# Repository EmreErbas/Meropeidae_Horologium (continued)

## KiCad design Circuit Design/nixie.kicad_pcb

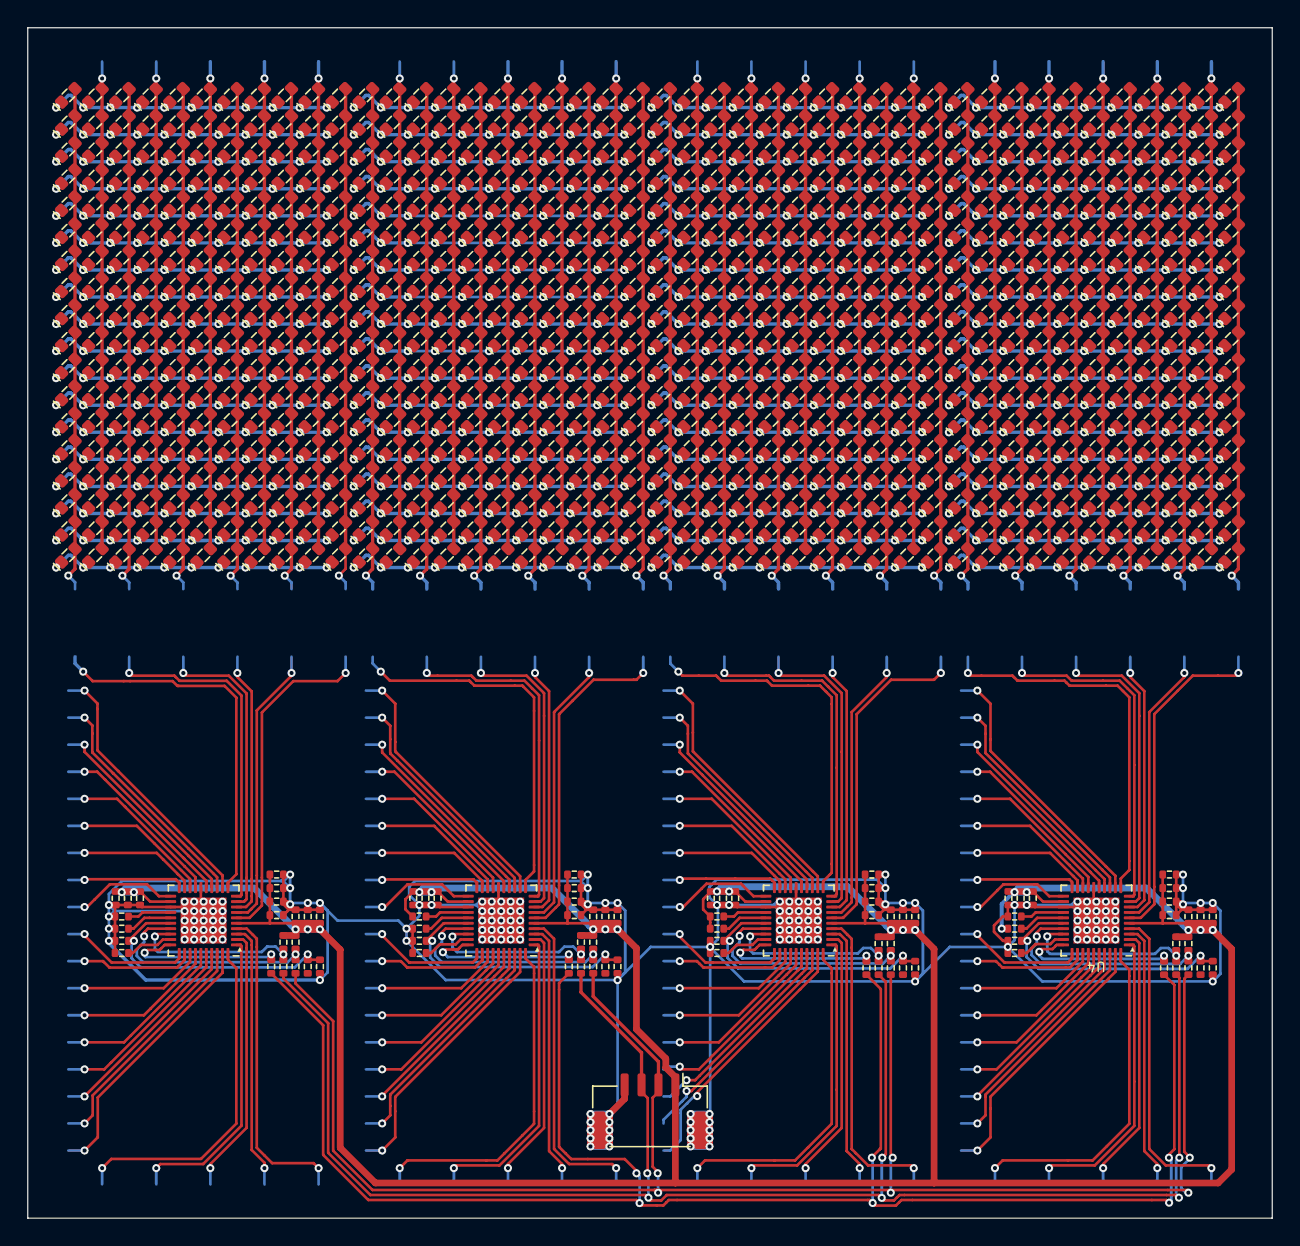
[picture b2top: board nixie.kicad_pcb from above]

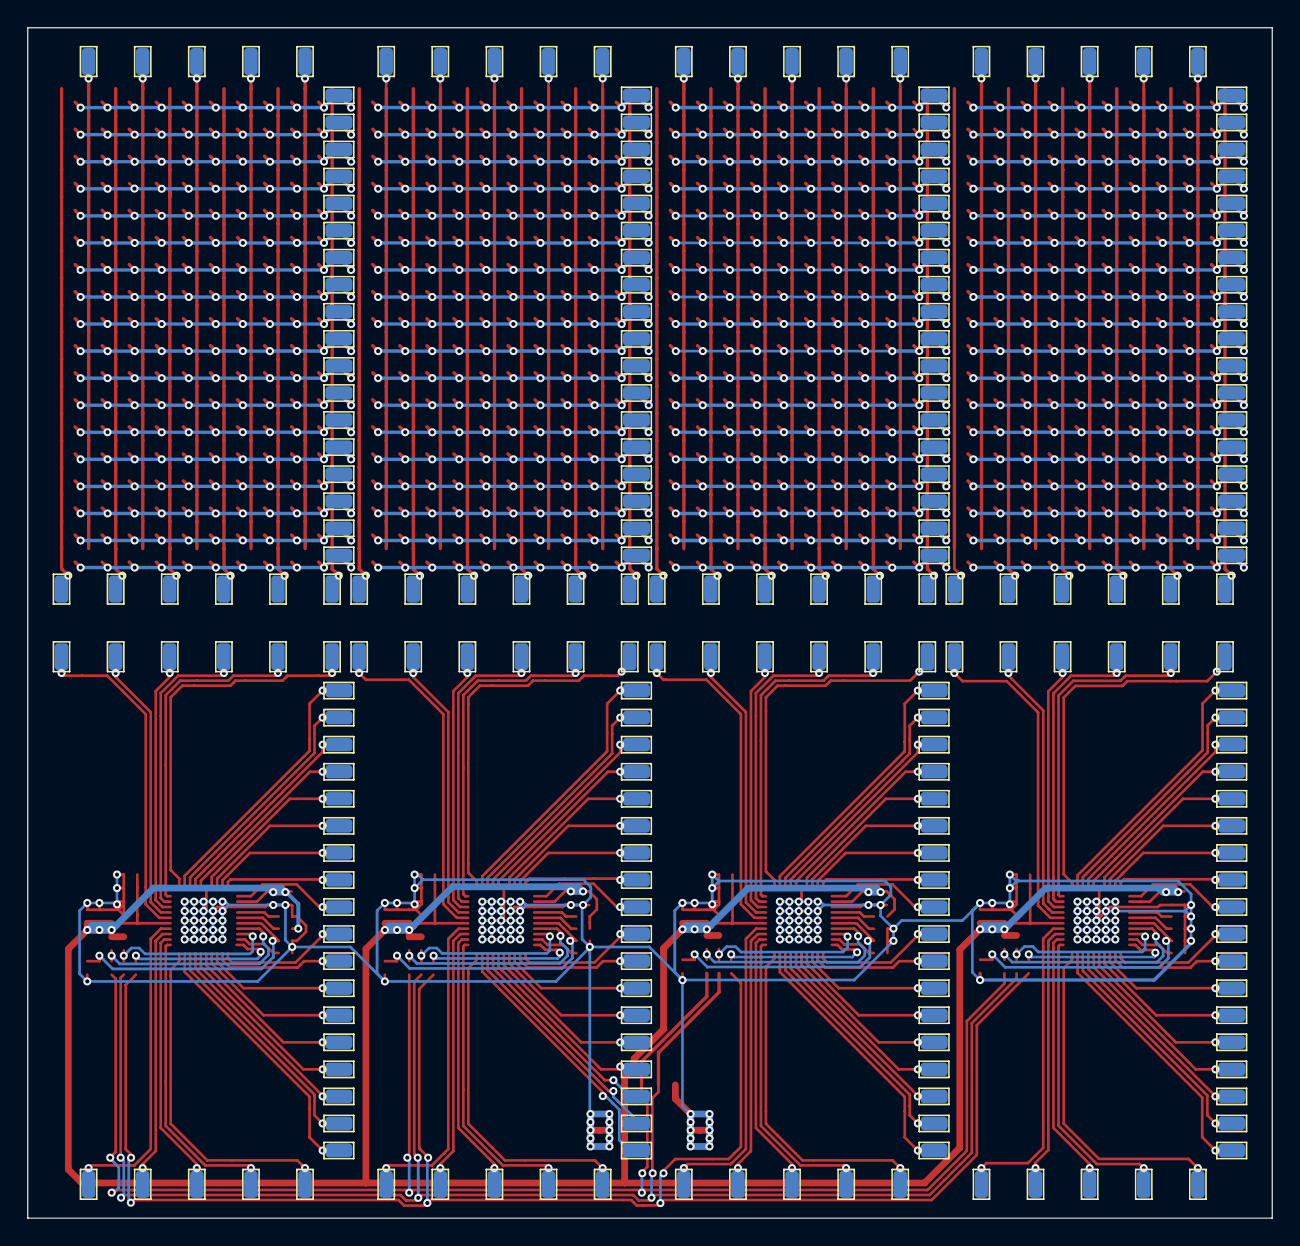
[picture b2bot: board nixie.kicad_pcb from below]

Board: 2 copper layers, 92.0 x 88.0 mm, 1113 parts (232 on the bottom side), 265 nets.

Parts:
C1, C2, C3, C4, C5, C6, C7, C8, C9, C10, C11, C12, C13, C16, C20, C23, C27, C30, C34, C35, C36, C37, C38, C41: 1uF; C-0402
C14, C15, C17, C18, C19, C21, C22, C24, C25, C26, C28, C29, C31, C32, C33, C39, C40, C42, C43, C44: 100nF; C-0402
CP1, CP2, CP3, CP4, CP5, CP6, CP7, CP8, CP9, CP10, CP11, CP12, CP13, CP14, CP15, CP16, CP17, CP18, CP19, CP20, CP21, CP22, CP23, CP24, CP25, CP26, CP27, CP28, CP29, CP30, CP31, CP32, CP33, CP34, CP35, CP36, CP37, CP38, CP39, CP40, CP41, CP42, CP43, CP44, CP45, CP46, CP47, CP48, CP49, CP50, CP51, CP52, CP53, CP54, CP55, CP56, CP57, CP58, CP59, CP60, CP61, CP62, CP63, CP64, CP65, CP66, CP67, CP68, CP69, CP70, CP71, CP72, CP73, CP74, CP75, CP76, CP77, CP78, CP79, CP80, CP81, CP82, CP83, CP84, CP85, CP86, CP87, CP88, CP89, CP90, CP91, CP92, CP93, CP94, CP95, CP96, CP97, CP98, CP99, CP100, CP101, CP102, CP103, CP104, CP105, CP106, CP107, CP108, CP109, CP110, CP111, CP112, CP113, CP114, CP115, CP116, CP117, CP118, CP119, CP120, CP121, CP122, CP123, CP124, CP125, CP126, CP127, CP128, CP129, CP130, CP131, CP132, CP133, CP134, CP135, CP136, CP137, CP138, CP139, CP140, CP141, CP142, CP143, CP144, CP145, CP146, CP147, CP148, CP149, CP150, CP151, CP152, CP153, CP154, CP155, CP156, CP157, CP158, CP159, CP160, CP161, CP162, CP163, CP164, CP165, CP166, CP167, CP168, CP169, CP170, CP171, CP172, CP173, CP174, CP175, CP176, CP177, CP178, CP179, CP180, CP181, CP182, CP183, CP184, CP185, CP186, CP187, CP188, CP189, CP190, CP191, CP192, CP193, CP194, CP195, CP196, CP197, CP198, CP199, CP200, CP201, CP202, CP203, CP204, CP205, CP206, CP207, CP208, CP209, CP210, CP211, CP212, CP213, CP214, CP215, CP216, CP217, CP218, CP219, CP220, CP221, CP222, CP223, CP224, CP225, CP226, CP227, CP228, CP229, CP230, CP231, CP232: SolderPad; SolderPt_1x2mm
D1, D2, D3, D4, D5, D6, D7, D8, D9, D10, D11, D12, D13, D14, D15, D16, D17, D18, D19, D20, D21, D22, D23, D24, D25, D26, D27, D28, D29, D30, D31, D32, D33, D34, D35, D36, D37, D38, D39, D40, D41, D42, D43, D44, D45, D46, D47, D48, D49, D50, D51, D52, D53, D54, D55, D56, D57, D58, D59, D60, D61, D62, D63, D64, D65, D66, D67, D68, D69, D70, D71, D72, D73, D74, D75, D76, D77, D78, D79, D80, D81, D82, D83, D84, D85, D86, D87, D88, D89, D90, D91, D92, D93, D94, D95, D96, D97, D98, D99, D100, D101, D102, D103, D104, D105, D106, D107, D108, D109, D110, D111, D112, D113, D114, D115, D116, D117, D118, D119, D120, D121, D122, D123, D124, D125, D126, D127, D128, D129, D130, D131, D132, D133, D134, D135, D136, D137, D138, D139, D140, D141, D142, D143, D144, D145, D146, D147, D148, D149, D150, D151, D152, D153, D154, D155, D156, D157, D158, D159, D160, D161, D162, D163, D164, D165, D166, D167, D168, D169, D170, D171, D172, D173, D174, D175, D176, D177, D178, D179, D180, D181, D182, D183, D184, D185, D186, D187, D188, D189, D190, D191, D192, D193, D194, D195, D196, D197, D198, D199, D200, D201, D202, D203, D204, D205, D206, D207, D208, D209, D210, D211, D212, D213, D214, D215, D216, D217, D218, D219, D220, D221, D222, D223, D224, D225, D226, D227, D228, D229, D230, D231, D232, D233, D234, D235, D236, D237, D238, D239, D240, D241, D242, D243, D244, D245, D246, D247, D248, D249, D250, D251, D252, D253, D254, D255, D256, D257, D258, D259, D260, D261, D262, D263, D264, D265, D266, D267, D268, D269, D270, D271, D272, D273, D274, D275, D276, D277, D278, D279, D280, D281, D282, D283, D284, D285, D286, D287, D288, D289, D290, D291, D292, D293, D294, D295, D296, D297, D298, D299, D300, D301, D302, D303, D304, D305, D306, D307, D308, D309, D310, D311, D312, D313, D314, D315, D316, D317, D318, D319, D320, D321, D322, D323, D324, D325, D326, D327, D328, D329, D330, D331, D332, D333, D334, D335, D336, D337, D338, D339, D340, D341, D342, D343, D344, D345, D346, D347, D348, D349, D350, D351, D352, D353, D354, D355, D356, D357, D358, D359, D360, D361, D362, D363, D364, D365, D366, D367, D368, D369, D370, D371, D372, D373, D374, D375, D376, D377, D378, D379, D380, D381, D382, D383, D384, D385, D386, D387, D388, D389, D390, D391, D392, D393, D394, D395, D396, D397, D398, D399, D400, D401, D402, D403, D404, D405, D406, D407, D408, D409, D410, D411, D412, D413, D414, D415, D416, D417, D418, D419, D420, D421, D422, D423, D424, D425, D426, D427, D428, D429, D430, D431, D432, D433, D434, D435, D436, D437, D438, D439, D440, D441, D442, D443, D444, D445, D446, D447, D448, D449, D450, D451, D452, D453, D454, D455, D456, D457, D458, D459, D460, D461, D462, D463, D464, D465, D466, D467, D468, D469, D470, D471, D472, D473, D474, D475, D476, D477, D478, D479, D480, D481, D482, D483, D484, D485, D486, D487, D488, D489, D490, D491, D492, D493, D494, D495, D496, D497, D498, D499, D500, D501, D502, D503, D504, D505, D506, D507, D508, D509, D510, D511, D512, D513, D514, D515, D516, D517, D518, D519, D520, D521, D522, D523, D524, D525, D526, D527, D528, D529, D530, D531, D532, D533, D534, D535, D536, D537, D538, D539, D540, D541, D542, D543, D544, D545, D546, D547, D548, D549, D550, D551, D552, D553, D554, D555, D556, D557, D558, D559, D560, D561, D562, D563, D564, D565, D566, D567, D568, D569, D570, D571, D572, D573, D574, D575, D576, D577, D578, D579, D580, D581, D582, D583, D584, D585, D586, D587, D588, D589, D590, D591, D592, D593, D594, D595, D596, D597, D598, D599, D600, D601, D602, D603, D604, D605, D606, D607, D608, D609, D610, D611, D612, D613, D614, D615, D616, D617, D618, D619, D620, D621, D622, D623, D624, D625, D626, D627, D628, D629, D630, D631, D632, D633, D634, D635, D636, D637, D638, D639, D640, D641, D642, D643, D644, D645, D646, D647, D648, D649, D650, D651, D652, D653, D654, D655, D656, D657, D658, D659, D660, D661, D662, D663, D664, D665, D666, D667, D668, D669, D670, D671, D672, D673, D674, D675, D676, D677, D678, D679, D680, D681, D682, D683, D684, D685, D686, D687, D688, D689, D690, D691, D692, D693, D694, D695, D696, D697, D698, D699, D700, D701, D702, D703, D704, D705, D706, D707, D708, D709, D710, D711, D712, D713, D714, D715, D716, D717, D718, D719, D720, D721, D722, D723, D724, D725, D726, D727, D728, D729, D730, D731, D732, D733, D734, D735, D736, D737, D738, D739, D740, D741, D742, D743, D744, D745, D746, D747, D748, D749, D750, D751, D752, D753, D754, D755, D756, D757, D758, D759, D760, D761, D762, D763, D764, D765, D766, D767, D768, D769, D770, D771, D772, D773, D774, D775, D776, D777, D778, D779, D780, D781, D782, D783, D784, D785, D786, D787, D788, D789, D790, D791, D792: LED_A; LED-0603
J1: BM04B-GHS-TBT
R1, R2, R11, R12, R21, R22, R31, R32: 10K; R-0402
R3, R4, R5, R13, R14, R15, R23, R24, R25, R33, R34, R35: 22R; R-0402
R6, R16, R26, R36: 100K; R-0402
R7, R9, R10, R17, R19, R20, R27, R29, R30, R37, R39, R40: 0R; R-0402
R8, R18, R28, R38: 18K; R-0402
U1, U2, U3, U4: IS31FL3743A; QFN-40-EP

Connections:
+3V3: C1.1, C2.1, C3.1, C4.1, C5.1, C6.1, C7.1, C8.1, C9.1, C10.1, C11.1, C12.1, C13.1, C14.1, C15.1, C16.1, C17.1, C18.1, C20.1, C21.1, C22.1, C23.1, C24.1, C25.1, C27.1, C28.1, C29.1, C30.1, C31.1, C32.1, C34.1, C35.1, C36.1, C37.1, C38.1, C39.1, C40.1, C41.1, C42.1, C43.1, J1.1, R1.1, R2.1, R11.1, R12.1, R19.1, R21.1, R22.1, R29.1, R30.1, R31.1, R32.1, R40.1, U1.5 (PVCC), U1.22 (VCC), U2.5 (PVCC), U2.22 (VCC), U3.5 (PVCC), U3.22 (VCC), U4.5 (PVCC), U4.22 (VCC)
/LED Driver1/CS1: CP171.1, U2.39 (CS1)
/LED Driver1/CS2: CP165.1, U2.38 (CS2)
/LED Driver1/CS3: CP159.1, U2.37 (CS3)
/LED Driver1/CS4: CP153.1, U2.36 (CS4)
/LED Driver1/CS5: CP147.1, U2.35 (CS5)
/LED Driver1/CS6: CP141.1, U2.34 (CS6)
/LED Driver1/CS7: CP135.1, U2.33 (CS7)
/LED Driver1/CS8: CP129.1, U2.32 (CS8)
/LED Driver1/CS9: CP123.1, U2.31 (CS9)
/LED Driver1/CS10: CP117.1, U2.21 (CS10)
/LED Driver1/CS11: CP111.1, U2.20 (CS11)
/LED Driver1/CS12: CP105.1, U2.19 (CS12)
/LED Driver1/CS13: CP99.1, U2.18 (CS13)
/LED Driver1/CS14: CP93.1, U2.17 (CS14)
/LED Driver1/CS15: CP87.1, U2.15 (CS15)
/LED Driver1/CS16: CP81.1, U2.14 (CS16)
/LED Driver1/CS17: CP75.1, U2.13 (CS17)
/LED Driver1/CS18: CP69.1, U2.12 (CS18)
/LED Driver1/SW1: CP3.1, U2.6 (SW1)
/LED Driver1/SW2: CP9.1, U2.4 (SW2)
/LED Driver1/SW3: CP15.1, U2.7 (SW3)
/LED Driver1/SW4: CP21.1, U2.3 (SW4)
/LED Driver1/SW5: CP27.1, U2.8 (SW5)
/LED Driver1/SW6: CP33.1, U2.2 (SW6)
/LED Driver1/SW7: CP39.1, U2.9 (SW7)
/LED Driver1/SW8: CP45.1, U2.1 (SW8)
/LED Driver1/SW9: CP51.1, U2.10 (SW9)
/LED Driver1/SW10: CP57.1, U2.40 (SW10)
/LED Driver1/SW11: CP63.1, U2.11 (SW11)
/LED Driver2/CS1: CP173.1, U3.39 (CS1)
/LED Driver2/CS2: CP167.1, U3.38 (CS2)
/LED Driver2/CS3: CP161.1, U3.37 (CS3)
/LED Driver2/CS4: CP155.1, U3.36 (CS4)
/LED Driver2/CS5: CP149.1, U3.35 (CS5)
/LED Driver2/CS6: CP143.1, U3.34 (CS6)
/LED Driver2/CS7: CP137.1, U3.33 (CS7)
/LED Driver2/CS8: CP131.1, U3.32 (CS8)
/LED Driver2/CS9: CP125.1, U3.31 (CS9)
/LED Driver2/CS10: CP119.1, U3.21 (CS10)
/LED Driver2/CS11: CP113.1, U3.20 (CS11)
/LED Driver2/CS12: CP107.1, U3.19 (CS12)
/LED Driver2/CS13: CP101.1, U3.18 (CS13)
/LED Driver2/CS14: CP95.1, U3.17 (CS14)
/LED Driver2/CS15: CP89.1, U3.15 (CS15)
/LED Driver2/CS16: CP83.1, U3.14 (CS16)
/LED Driver2/CS17: CP77.1, U3.13 (CS17)
/LED Driver2/CS18: CP71.1, U3.12 (CS18)
/LED Driver2/SW1: CP5.1, U3.6 (SW1)
/LED Driver2/SW2: CP11.1, U3.4 (SW2)
/LED Driver2/SW3: CP17.1, U3.7 (SW3)
/LED Driver2/SW4: CP23.1, U3.3 (SW4)
/LED Driver2/SW5: CP29.1, U3.8 (SW5)
/LED Driver2/SW6: CP35.1, U3.2 (SW6)
/LED Driver2/SW7: CP41.1, U3.9 (SW7)
/LED Driver2/SW8: CP47.1, U3.1 (SW8)
/LED Driver2/SW9: CP53.1, U3.10 (SW9)
/LED Driver2/SW10: CP59.1, U3.40 (SW10)
/LED Driver2/SW11: CP65.1, U3.11 (SW11)
/LED Driver3/CS1: CP231.1, U4.39 (CS1)
/LED Driver3/CS2: CP229.1, U4.38 (CS2)
/LED Driver3/CS3: CP227.1, U4.37 (CS3)
/LED Driver3/CS4: CP225.1, U4.36 (CS4)
/LED Driver3/CS5: CP223.1, U4.35 (CS5)
/LED Driver3/CS6: CP221.1, U4.34 (CS6)
/LED Driver3/CS7: CP219.1, U4.33 (CS7)
/LED Driver3/CS8: CP217.1, U4.32 (CS8)
/LED Driver3/CS9: CP215.1, U4.31 (CS9)
/LED Driver3/CS10: CP213.1, U4.21 (CS10)
/LED Driver3/CS11: CP211.1, U4.20 (CS11)
/LED Driver3/CS12: CP209.1, U4.19 (CS12)
/LED Driver3/CS13: CP207.1, U4.18 (CS13)
/LED Driver3/CS14: CP205.1, U4.17 (CS14)
/LED Driver3/CS15: CP203.1, U4.15 (CS15)
/LED Driver3/CS16: CP201.1, U4.14 (CS16)
/LED Driver3/CS17: CP199.1, U4.13 (CS17)
/LED Driver3/CS18: CP197.1, U4.12 (CS18)
/LED Driver3/SW1: CP175.1, U4.6 (SW1)
/LED Driver3/SW2: CP177.1, U4.4 (SW2)
/LED Driver3/SW3: CP179.1, U4.7 (SW3)
/LED Driver3/SW4: CP181.1, U4.3 (SW4)
/LED Driver3/SW5: CP183.1, U4.8 (SW5)
/LED Driver3/SW6: CP185.1, U4.2 (SW6)
/LED Driver3/SW7: CP187.1, U4.9 (SW7)
/LED Driver3/SW8: CP189.1, U4.1 (SW8)
/LED Driver3/SW9: CP191.1, U4.10 (SW9)
/LED Driver3/SW10: CP193.1, U4.40 (SW10)
/LED Driver3/SW11: CP195.1, U4.11 (SW11)
/LED Driver/CS1: CP169.1, U1.39 (CS1)
/LED Driver/CS2: CP163.1, U1.38 (CS2)
/LED Driver/CS3: CP157.1, U1.37 (CS3)
/LED Driver/CS4: CP151.1, U1.36 (CS4)
/LED Driver/CS5: CP145.1, U1.35 (CS5)
/LED Driver/CS6: CP139.1, U1.34 (CS6)
/LED Driver/CS7: CP133.1, U1.33 (CS7)
/LED Driver/CS8: CP127.1, U1.32 (CS8)
/LED Driver/CS9: CP121.1, U1.31 (CS9)
/LED Driver/CS10: CP115.1, U1.21 (CS10)
/LED Driver/CS11: CP109.1, U1.20 (CS11)
/LED Driver/CS12: CP103.1, U1.19 (CS12)
/LED Driver/CS13: CP97.1, U1.18 (CS13)
/LED Driver/CS14: CP91.1, U1.17 (CS14)
/LED Driver/CS15: CP85.1, U1.15 (CS15)
/LED Driver/CS16: CP79.1, U1.14 (CS16)
/LED Driver/CS17: CP73.1, U1.13 (CS17)
/LED Driver/CS18: CP67.1, U1.12 (CS18)
/LED Driver/SW1: CP1.1, U1.6 (SW1)
/LED Driver/SW2: CP7.1, U1.4 (SW2)
/LED Driver/SW3: CP13.1, U1.7 (SW3)
/LED Driver/SW4: CP19.1, U1.3 (SW4)
/LED Driver/SW5: CP25.1, U1.8 (SW5)
/LED Driver/SW6: CP31.1, U1.2 (SW6)
/LED Driver/SW7: CP37.1, U1.9 (SW7)
/LED Driver/SW8: CP43.1, U1.1 (SW8)
/LED Driver/SW9: CP49.1, U1.10 (SW9)
/LED Driver/SW10: CP55.1, U1.40 (SW10)
/LED Driver/SW11: CP61.1, U1.11 (SW11)
/SCL: J1.2, R4.1, R14.1, R24.1, R34.1
/SDA: J1.3, R3.1, R13.1, R23.1, R33.1
/SYNC: R7.1, R17.1, R27.1, R37.1
/Screen1/CS1: CP172.1, D199.1 (K), D217.1 (K), D235.1 (K), D253.1 (K), D271.1 (K), D289.1 (K), D307.1 (K), D325.1 (K), D343.1 (K), D361.1 (K), D379.1 (K)
/Screen1/CS2: CP166.1, D200.1 (K), D218.1 (K), D236.1 (K), D254.1 (K), D272.1 (K), D290.1 (K), D308.1 (K), D326.1 (K), D344.1 (K), D362.1 (K), D380.1 (K)
/Screen1/CS3: CP160.1, D201.1 (K), D219.1 (K), D237.1 (K), D255.1 (K), D273.1 (K), D291.1 (K), D309.1 (K), D327.1 (K), D345.1 (K), D363.1 (K), D381.1 (K)
/Screen1/CS4: CP154.1, D202.1 (K), D220.1 (K), D238.1 (K), D256.1 (K), D274.1 (K), D292.1 (K), D310.1 (K), D328.1 (K), D346.1 (K), D364.1 (K), D382.1 (K)
/Screen1/CS5: CP148.1, D203.1 (K), D221.1 (K), D239.1 (K), D257.1 (K), D275.1 (K), D293.1 (K), D311.1 (K), D329.1 (K), D347.1 (K), D365.1 (K), D383.1 (K)
/Screen1/CS6: CP142.1, D204.1 (K), D222.1 (K), D240.1 (K), D258.1 (K), D276.1 (K), D294.1 (K), D312.1 (K), D330.1 (K), D348.1 (K), D366.1 (K), D384.1 (K)
/Screen1/CS7: CP136.1, D205.1 (K), D223.1 (K), D241.1 (K), D259.1 (K), D277.1 (K), D295.1 (K), D313.1 (K), D331.1 (K), D349.1 (K), D367.1 (K), D385.1 (K)
/Screen1/CS8: CP130.1, D206.1 (K), D224.1 (K), D242.1 (K), D260.1 (K), D278.1 (K), D296.1 (K), D314.1 (K), D332.1 (K), D350.1 (K), D368.1 (K), D386.1 (K)
/Screen1/CS9: CP124.1, D207.1 (K), D225.1 (K), D243.1 (K), D261.1 (K), D279.1 (K), D297.1 (K), D315.1 (K), D333.1 (K), D351.1 (K), D369.1 (K), D387.1 (K)
/Screen1/CS10: CP118.1, D208.1 (K), D226.1 (K), D244.1 (K), D262.1 (K), D280.1 (K), D298.1 (K), D316.1 (K), D334.1 (K), D352.1 (K), D370.1 (K), D388.1 (K)
/Screen1/CS11: CP112.1, D209.1 (K), D227.1 (K), D245.1 (K), D263.1 (K), D281.1 (K), D299.1 (K), D317.1 (K), D335.1 (K), D353.1 (K), D371.1 (K), D389.1 (K)
/Screen1/CS12: CP106.1, D210.1 (K), D228.1 (K), D246.1 (K), D264.1 (K), D282.1 (K), D300.1 (K), D318.1 (K), D336.1 (K), D354.1 (K), D372.1 (K), D390.1 (K)
/Screen1/CS13: CP100.1, D211.1 (K), D229.1 (K), D247.1 (K), D265.1 (K), D283.1 (K), D301.1 (K), D319.1 (K), D337.1 (K), D355.1 (K), D373.1 (K), D391.1 (K)
/Screen1/CS14: CP94.1, D212.1 (K), D230.1 (K), D248.1 (K), D266.1 (K), D284.1 (K), D302.1 (K), D320.1 (K), D338.1 (K), D356.1 (K), D374.1 (K), D392.1 (K)
/Screen1/CS15: CP88.1, D213.1 (K), D231.1 (K), D249.1 (K), D267.1 (K), D285.1 (K), D303.1 (K), D321.1 (K), D339.1 (K), D357.1 (K), D375.1 (K), D393.1 (K)
/Screen1/CS16: CP82.1, D214.1 (K), D232.1 (K), D250.1 (K), D268.1 (K), D286.1 (K), D304.1 (K), D322.1 (K), D340.1 (K), D358.1 (K), D376.1 (K), D394.1 (K)
/Screen1/CS17: CP76.1, D215.1 (K), D233.1 (K), D251.1 (K), D269.1 (K), D287.1 (K), D305.1 (K), D323.1 (K), D341.1 (K), D359.1 (K), D377.1 (K), D395.1 (K)
/Screen1/CS18: CP70.1, D216.1 (K), D234.1 (K), D252.1 (K), D270.1 (K), D288.1 (K), D306.1 (K), D324.1 (K), D342.1 (K), D360.1 (K), D378.1 (K), D396.1 (K)
/Screen1/SW1: CP64.1, D199.2 (A), D200.2 (A), D201.2 (A), D202.2 (A), D203.2 (A), D204.2 (A), D205.2 (A), D206.2 (A), D207.2 (A), D208.2 (A), D209.2 (A), D210.2 (A), D211.2 (A), D212.2 (A), D213.2 (A), D214.2 (A), D215.2 (A), D216.2 (A)
/Screen1/SW2: CP58.1, D217.2 (A), D218.2 (A), D219.2 (A), D220.2 (A), D221.2 (A), D222.2 (A), D223.2 (A), D224.2 (A), D225.2 (A), D226.2 (A), D227.2 (A), D228.2 (A), D229.2 (A), D230.2 (A), D231.2 (A), D232.2 (A), D233.2 (A), D234.2 (A)
/Screen1/SW3: CP52.1, D235.2 (A), D236.2 (A), D237.2 (A), D238.2 (A), D239.2 (A), D240.2 (A), D241.2 (A), D242.2 (A), D243.2 (A), D244.2 (A), D245.2 (A), D246.2 (A), D247.2 (A), D248.2 (A), D249.2 (A), D250.2 (A), D251.2 (A), D252.2 (A)
/Screen1/SW4: CP46.1, D253.2 (A), D254.2 (A), D255.2 (A), D256.2 (A), D257.2 (A), D258.2 (A), D259.2 (A), D260.2 (A), D261.2 (A), D262.2 (A), D263.2 (A), D264.2 (A), D265.2 (A), D266.2 (A), D267.2 (A), D268.2 (A), D269.2 (A), D270.2 (A)
/Screen1/SW5: CP40.1, D271.2 (A), D272.2 (A), D273.2 (A), D274.2 (A), D275.2 (A), D276.2 (A), D277.2 (A), D278.2 (A), D279.2 (A), D280.2 (A), D281.2 (A), D282.2 (A), D283.2 (A), D284.2 (A), D285.2 (A), D286.2 (A), D287.2 (A), D288.2 (A)
/Screen1/SW6: CP34.1, D289.2 (A), D290.2 (A), D291.2 (A), D292.2 (A), D293.2 (A), D294.2 (A), D295.2 (A), D296.2 (A), D297.2 (A), D298.2 (A), D299.2 (A), D300.2 (A), D301.2 (A), D302.2 (A), D303.2 (A), D304.2 (A), D305.2 (A), D306.2 (A)
/Screen1/SW7: CP28.1, D307.2 (A), D308.2 (A), D309.2 (A), D310.2 (A), D311.2 (A), D312.2 (A), D313.2 (A), D314.2 (A), D315.2 (A), D316.2 (A), D317.2 (A), D318.2 (A), D319.2 (A), D320.2 (A), D321.2 (A), D322.2 (A), D323.2 (A), D324.2 (A)
/Screen1/SW8: CP22.1, D325.2 (A), D326.2 (A), D327.2 (A), D328.2 (A), D329.2 (A), D330.2 (A), D331.2 (A), D332.2 (A), D333.2 (A), D334.2 (A), D335.2 (A), D336.2 (A), D337.2 (A), D338.2 (A), D339.2 (A), D340.2 (A), D341.2 (A), D342.2 (A)
/Screen1/SW9: CP16.1, D343.2 (A), D344.2 (A), D345.2 (A), D346.2 (A), D347.2 (A), D348.2 (A), D349.2 (A), D350.2 (A), D351.2 (A), D352.2 (A), D353.2 (A), D354.2 (A), D355.2 (A), D356.2 (A), D357.2 (A), D358.2 (A), D359.2 (A), D360.2 (A)
/Screen1/SW10: CP10.1, D361.2 (A), D362.2 (A), D363.2 (A), D364.2 (A), D365.2 (A), D366.2 (A), D367.2 (A), D368.2 (A), D369.2 (A), D370.2 (A), D371.2 (A), D372.2 (A), D373.2 (A), D374.2 (A), D375.2 (A), D376.2 (A), D377.2 (A), D378.2 (A)
/Screen1/SW11: CP4.1, D379.2 (A), D380.2 (A), D381.2 (A), D382.2 (A), D383.2 (A), D384.2 (A), D385.2 (A), D386.2 (A), D387.2 (A), D388.2 (A), D389.2 (A), D390.2 (A), D391.2 (A), D392.2 (A), D393.2 (A), D394.2 (A), D395.2 (A), D396.2 (A)
/Screen2/CS1: CP174.1, D397.1 (K), D415.1 (K), D433.1 (K), D451.1 (K), D469.1 (K), D487.1 (K), D505.1 (K), D523.1 (K), D541.1 (K), D559.1 (K), D577.1 (K)
/Screen2/CS2: CP168.1, D398.1 (K), D416.1 (K), D434.1 (K), D452.1 (K), D470.1 (K), D488.1 (K), D506.1 (K), D524.1 (K), D542.1 (K), D560.1 (K), D578.1 (K)
/Screen2/CS3: CP162.1, D399.1 (K), D417.1 (K), D435.1 (K), D453.1 (K), D471.1 (K), D489.1 (K), D507.1 (K), D525.1 (K), D543.1 (K), D561.1 (K), D579.1 (K)
/Screen2/CS4: CP156.1, D400.1 (K), D418.1 (K), D436.1 (K), D454.1 (K), D472.1 (K), D490.1 (K), D508.1 (K), D526.1 (K), D544.1 (K), D562.1 (K), D580.1 (K)
/Screen2/CS5: CP150.1, D401.1 (K), D419.1 (K), D437.1 (K), D455.1 (K), D473.1 (K), D491.1 (K), D509.1 (K), D527.1 (K), D545.1 (K), D563.1 (K), D581.1 (K)
/Screen2/CS6: CP144.1, D402.1 (K), D420.1 (K), D438.1 (K), D456.1 (K), D474.1 (K), D492.1 (K), D510.1 (K), D528.1 (K), D546.1 (K), D564.1 (K), D582.1 (K)
/Screen2/CS7: CP138.1, D403.1 (K), D421.1 (K), D439.1 (K), D457.1 (K), D475.1 (K), D493.1 (K), D511.1 (K), D529.1 (K), D547.1 (K), D565.1 (K), D583.1 (K)
/Screen2/CS8: CP132.1, D404.1 (K), D422.1 (K), D440.1 (K), D458.1 (K), D476.1 (K), D494.1 (K), D512.1 (K), D530.1 (K), D548.1 (K), D566.1 (K), D584.1 (K)
/Screen2/CS9: CP126.1, D405.1 (K), D423.1 (K), D441.1 (K), D459.1 (K), D477.1 (K), D495.1 (K), D513.1 (K), D531.1 (K), D549.1 (K), D567.1 (K), D585.1 (K)
/Screen2/CS10: CP120.1, D406.1 (K), D424.1 (K), D442.1 (K), D460.1 (K), D478.1 (K), D496.1 (K), D514.1 (K), D532.1 (K), D550.1 (K), D568.1 (K), D586.1 (K)
/Screen2/CS11: CP114.1, D407.1 (K), D425.1 (K), D443.1 (K), D461.1 (K), D479.1 (K), D497.1 (K), D515.1 (K), D533.1 (K), D551.1 (K), D569.1 (K), D587.1 (K)
/Screen2/CS12: CP108.1, D408.1 (K), D426.1 (K), D444.1 (K), D462.1 (K), D480.1 (K), D498.1 (K), D516.1 (K), D534.1 (K), D552.1 (K), D570.1 (K), D588.1 (K)
/Screen2/CS13: CP102.1, D409.1 (K), D427.1 (K), D445.1 (K), D463.1 (K), D481.1 (K), D499.1 (K), D517.1 (K), D535.1 (K), D553.1 (K), D571.1 (K), D589.1 (K)
/Screen2/CS14: CP96.1, D410.1 (K), D428.1 (K), D446.1 (K), D464.1 (K), D482.1 (K), D500.1 (K), D518.1 (K), D536.1 (K), D554.1 (K), D572.1 (K), D590.1 (K)
/Screen2/CS15: CP90.1, D411.1 (K), D429.1 (K), D447.1 (K), D465.1 (K), D483.1 (K), D501.1 (K), D519.1 (K), D537.1 (K), D555.1 (K), D573.1 (K), D591.1 (K)
/Screen2/CS16: CP84.1, D412.1 (K), D430.1 (K), D448.1 (K), D466.1 (K), D484.1 (K), D502.1 (K), D520.1 (K), D538.1 (K), D556.1 (K), D574.1 (K), D592.1 (K)
/Screen2/CS17: CP78.1, D413.1 (K), D431.1 (K), D449.1 (K), D467.1 (K), D485.1 (K), D503.1 (K), D521.1 (K), D539.1 (K), D557.1 (K), D575.1 (K), D593.1 (K)
/Screen2/CS18: CP72.1, D414.1 (K), D432.1 (K), D450.1 (K), D468.1 (K), D486.1 (K), D504.1 (K), D522.1 (K), D540.1 (K), D558.1 (K), D576.1 (K), D594.1 (K)
/Screen2/SW1: CP66.1, D397.2 (A), D398.2 (A), D399.2 (A), D400.2 (A), D401.2 (A), D402.2 (A), D403.2 (A), D404.2 (A), D405.2 (A), D406.2 (A), D407.2 (A), D408.2 (A), D409.2 (A), D410.2 (A), D411.2 (A), D412.2 (A), D413.2 (A), D414.2 (A)
/Screen2/SW2: CP60.1, D415.2 (A), D416.2 (A), D417.2 (A), D418.2 (A), D419.2 (A), D420.2 (A), D421.2 (A), D422.2 (A), D423.2 (A), D424.2 (A), D425.2 (A), D426.2 (A), D427.2 (A), D428.2 (A), D429.2 (A), D430.2 (A), D431.2 (A), D432.2 (A)
/Screen2/SW3: CP54.1, D433.2 (A), D434.2 (A), D435.2 (A), D436.2 (A), D437.2 (A), D438.2 (A), D439.2 (A), D440.2 (A), D441.2 (A), D442.2 (A), D443.2 (A), D444.2 (A), D445.2 (A), D446.2 (A), D447.2 (A), D448.2 (A), D449.2 (A), D450.2 (A)
/Screen2/SW4: CP48.1, D451.2 (A), D452.2 (A), D453.2 (A), D454.2 (A), D455.2 (A), D456.2 (A), D457.2 (A), D458.2 (A), D459.2 (A), D460.2 (A), D461.2 (A), D462.2 (A), D463.2 (A), D464.2 (A), D465.2 (A), D466.2 (A), D467.2 (A), D468.2 (A)
/Screen2/SW5: CP42.1, D469.2 (A), D470.2 (A), D471.2 (A), D472.2 (A), D473.2 (A), D474.2 (A), D475.2 (A), D476.2 (A), D477.2 (A), D478.2 (A), D479.2 (A), D480.2 (A), D481.2 (A), D482.2 (A), D483.2 (A), D484.2 (A), D485.2 (A), D486.2 (A)
/Screen2/SW6: CP36.1, D487.2 (A), D488.2 (A), D489.2 (A), D490.2 (A), D491.2 (A), D492.2 (A), D493.2 (A), D494.2 (A), D495.2 (A), D496.2 (A), D497.2 (A), D498.2 (A), D499.2 (A), D500.2 (A), D501.2 (A), D502.2 (A), D503.2 (A), D504.2 (A)
/Screen2/SW7: CP30.1, D505.2 (A), D506.2 (A), D507.2 (A), D508.2 (A), D509.2 (A), D510.2 (A), D511.2 (A), D512.2 (A), D513.2 (A), D514.2 (A), D515.2 (A), D516.2 (A), D517.2 (A), D518.2 (A), D519.2 (A), D520.2 (A), D521.2 (A), D522.2 (A)
/Screen2/SW8: CP24.1, D523.2 (A), D524.2 (A), D525.2 (A), D526.2 (A), D527.2 (A), D528.2 (A), D529.2 (A), D530.2 (A), D531.2 (A), D532.2 (A), D533.2 (A), D534.2 (A), D535.2 (A), D536.2 (A), D537.2 (A), D538.2 (A), D539.2 (A), D540.2 (A)
/Screen2/SW9: CP18.1, D541.2 (A), D542.2 (A), D543.2 (A), D544.2 (A), D545.2 (A), D546.2 (A), D547.2 (A), D548.2 (A), D549.2 (A), D550.2 (A), D551.2 (A), D552.2 (A), D553.2 (A), D554.2 (A), D555.2 (A), D556.2 (A), D557.2 (A), D558.2 (A)
/Screen2/SW10: CP12.1, D559.2 (A), D560.2 (A), D561.2 (A), D562.2 (A), D563.2 (A), D564.2 (A), D565.2 (A), D566.2 (A), D567.2 (A), D568.2 (A), D569.2 (A), D570.2 (A), D571.2 (A), D572.2 (A), D573.2 (A), D574.2 (A), D575.2 (A), D576.2 (A)
/Screen2/SW11: CP6.1, D577.2 (A), D578.2 (A), D579.2 (A), D580.2 (A), D581.2 (A), D582.2 (A), D583.2 (A), D584.2 (A), D585.2 (A), D586.2 (A), D587.2 (A), D588.2 (A), D589.2 (A), D590.2 (A), D591.2 (A), D592.2 (A), D593.2 (A), D594.2 (A)
/Screen3/CS1: CP232.1, D595.1 (K), D613.1 (K), D631.1 (K), D649.1 (K), D667.1 (K), D685.1 (K), D703.1 (K), D721.1 (K), D739.1 (K), D757.1 (K), D775.1 (K)
/Screen3/CS2: CP230.1, D596.1 (K), D614.1 (K), D632.1 (K), D650.1 (K), D668.1 (K), D686.1 (K), D704.1 (K), D722.1 (K), D740.1 (K), D758.1 (K), D776.1 (K)
/Screen3/CS3: CP228.1, D597.1 (K), D615.1 (K), D633.1 (K), D651.1 (K), D669.1 (K), D687.1 (K), D705.1 (K), D723.1 (K), D741.1 (K), D759.1 (K), D777.1 (K)
/Screen3/CS4: CP226.1, D598.1 (K), D616.1 (K), D634.1 (K), D652.1 (K), D670.1 (K), D688.1 (K), D706.1 (K), D724.1 (K), D742.1 (K), D760.1 (K), D778.1 (K)
/Screen3/CS5: CP224.1, D599.1 (K), D617.1 (K), D635.1 (K), D653.1 (K), D671.1 (K), D689.1 (K), D707.1 (K), D725.1 (K), D743.1 (K), D761.1 (K), D779.1 (K)
/Screen3/CS6: CP222.1, D600.1 (K), D618.1 (K), D636.1 (K), D654.1 (K), D672.1 (K), D690.1 (K), D708.1 (K), D726.1 (K), D744.1 (K), D762.1 (K), D780.1 (K)
/Screen3/CS7: CP220.1, D601.1 (K), D619.1 (K), D637.1 (K), D655.1 (K), D673.1 (K), D691.1 (K), D709.1 (K), D727.1 (K), D745.1 (K), D763.1 (K), D781.1 (K)
/Screen3/CS8: CP218.1, D602.1 (K), D620.1 (K), D638.1 (K), D656.1 (K), D674.1 (K), D692.1 (K), D710.1 (K), D728.1 (K), D746.1 (K), D764.1 (K), D782.1 (K)
/Screen3/CS9: CP216.1, D603.1 (K), D621.1 (K), D639.1 (K), D657.1 (K), D675.1 (K), D693.1 (K), D711.1 (K), D729.1 (K), D747.1 (K), D765.1 (K), D783.1 (K)
/Screen3/CS10: CP214.1, D604.1 (K), D622.1 (K), D640.1 (K), D658.1 (K), D676.1 (K), D694.1 (K), D712.1 (K), D730.1 (K), D748.1 (K), D766.1 (K), D784.1 (K)
/Screen3/CS11: CP212.1, D605.1 (K), D623.1 (K), D641.1 (K), D659.1 (K), D677.1 (K), D695.1 (K), D713.1 (K), D731.1 (K), D749.1 (K), D767.1 (K), D785.1 (K)
/Screen3/CS12: CP210.1, D606.1 (K), D624.1 (K), D642.1 (K), D660.1 (K), D678.1 (K), D696.1 (K), D714.1 (K), D732.1 (K), D750.1 (K), D768.1 (K), D786.1 (K)
/Screen3/CS13: CP208.1, D607.1 (K), D625.1 (K), D643.1 (K), D661.1 (K), D679.1 (K), D697.1 (K), D715.1 (K), D733.1 (K), D751.1 (K), D769.1 (K), D787.1 (K)
/Screen3/CS14: CP206.1, D608.1 (K), D626.1 (K), D644.1 (K), D662.1 (K), D680.1 (K), D698.1 (K), D716.1 (K), D734.1 (K), D752.1 (K), D770.1 (K), D788.1 (K)
/Screen3/CS15: CP204.1, D609.1 (K), D627.1 (K), D645.1 (K), D663.1 (K), D681.1 (K), D699.1 (K), D717.1 (K), D735.1 (K), D753.1 (K), D771.1 (K), D789.1 (K)
/Screen3/CS16: CP202.1, D610.1 (K), D628.1 (K), D646.1 (K), D664.1 (K), D682.1 (K), D700.1 (K), D718.1 (K), D736.1 (K), D754.1 (K), D772.1 (K), D790.1 (K)
/Screen3/CS17: CP200.1, D611.1 (K), D629.1 (K), D647.1 (K), D665.1 (K), D683.1 (K), D701.1 (K), D719.1 (K), D737.1 (K), D755.1 (K), D773.1 (K), D791.1 (K)
/Screen3/CS18: CP198.1, D612.1 (K), D630.1 (K), D648.1 (K), D666.1 (K), D684.1 (K), D702.1 (K), D720.1 (K), D738.1 (K), D756.1 (K), D774.1 (K), D792.1 (K)
/Screen3/SW1: CP196.1, D595.2 (A), D596.2 (A), D597.2 (A), D598.2 (A), D599.2 (A), D600.2 (A), D601.2 (A), D602.2 (A), D603.2 (A), D604.2 (A), D605.2 (A), D606.2 (A), D607.2 (A), D608.2 (A), D609.2 (A), D610.2 (A), D611.2 (A), D612.2 (A)
/Screen3/SW2: CP194.1, D613.2 (A), D614.2 (A), D615.2 (A), D616.2 (A), D617.2 (A), D618.2 (A), D619.2 (A), D620.2 (A), D621.2 (A), D622.2 (A), D623.2 (A), D624.2 (A), D625.2 (A), D626.2 (A), D627.2 (A), D628.2 (A), D629.2 (A), D630.2 (A)
/Screen3/SW3: CP192.1, D631.2 (A), D632.2 (A), D633.2 (A), D634.2 (A), D635.2 (A), D636.2 (A), D637.2 (A), D638.2 (A), D639.2 (A), D640.2 (A), D641.2 (A), D642.2 (A), D643.2 (A), D644.2 (A), D645.2 (A), D646.2 (A), D647.2 (A), D648.2 (A)
/Screen3/SW4: CP190.1, D649.2 (A), D650.2 (A), D651.2 (A), D652.2 (A), D653.2 (A), D654.2 (A), D655.2 (A), D656.2 (A), D657.2 (A), D658.2 (A), D659.2 (A), D660.2 (A), D661.2 (A), D662.2 (A), D663.2 (A), D664.2 (A), D665.2 (A), D666.2 (A)
/Screen3/SW5: CP188.1, D667.2 (A), D668.2 (A), D669.2 (A), D670.2 (A), D671.2 (A), D672.2 (A), D673.2 (A), D674.2 (A), D675.2 (A), D676.2 (A), D677.2 (A), D678.2 (A), D679.2 (A), D680.2 (A), D681.2 (A), D682.2 (A), D683.2 (A), D684.2 (A)
/Screen3/SW6: CP186.1, D685.2 (A), D686.2 (A), D687.2 (A), D688.2 (A), D689.2 (A), D690.2 (A), D691.2 (A), D692.2 (A), D693.2 (A), D694.2 (A), D695.2 (A), D696.2 (A), D697.2 (A), D698.2 (A), D699.2 (A), D700.2 (A), D701.2 (A), D702.2 (A)
/Screen3/SW7: CP184.1, D703.2 (A), D704.2 (A), D705.2 (A), D706.2 (A), D707.2 (A), D708.2 (A), D709.2 (A), D710.2 (A), D711.2 (A), D712.2 (A), D713.2 (A), D714.2 (A), D715.2 (A), D716.2 (A), D717.2 (A), D718.2 (A), D719.2 (A), D720.2 (A)
/Screen3/SW8: CP182.1, D721.2 (A), D722.2 (A), D723.2 (A), D724.2 (A), D725.2 (A), D726.2 (A), D727.2 (A), D728.2 (A), D729.2 (A), D730.2 (A), D731.2 (A), D732.2 (A), D733.2 (A), D734.2 (A), D735.2 (A), D736.2 (A), D737.2 (A), D738.2 (A)
/Screen3/SW9: CP180.1, D739.2 (A), D740.2 (A), D741.2 (A), D742.2 (A), D743.2 (A), D744.2 (A), D745.2 (A), D746.2 (A), D747.2 (A), D748.2 (A), D749.2 (A), D750.2 (A), D751.2 (A), D752.2 (A), D753.2 (A), D754.2 (A), D755.2 (A), D756.2 (A)
/Screen3/SW10: CP178.1, D757.2 (A), D758.2 (A), D759.2 (A), D760.2 (A), D761.2 (A), D762.2 (A), D763.2 (A), D764.2 (A), D765.2 (A), D766.2 (A), D767.2 (A), D768.2 (A), D769.2 (A), D770.2 (A), D771.2 (A), D772.2 (A), D773.2 (A), D774.2 (A)
/Screen3/SW11: CP176.1, D775.2 (A), D776.2 (A), D777.2 (A), D778.2 (A), D779.2 (A), D780.2 (A), D781.2 (A), D782.2 (A), D783.2 (A), D784.2 (A), D785.2 (A), D786.2 (A), D787.2 (A), D788.2 (A), D789.2 (A), D790.2 (A), D791.2 (A), D792.2 (A)
/Screen/CS1: CP170.1, D1.1 (K), D19.1 (K), D37.1 (K), D55.1 (K), D73.1 (K), D91.1 (K), D109.1 (K), D127.1 (K), D145.1 (K), D163.1 (K), D181.1 (K)
/Screen/CS2: CP164.1, D2.1 (K), D20.1 (K), D38.1 (K), D56.1 (K), D74.1 (K), D92.1 (K), D110.1 (K), D128.1 (K), D146.1 (K), D164.1 (K), D182.1 (K)
/Screen/CS3: CP158.1, D3.1 (K), D21.1 (K), D39.1 (K), D57.1 (K), D75.1 (K), D93.1 (K), D111.1 (K), D129.1 (K), D147.1 (K), D165.1 (K), D183.1 (K)
/Screen/CS4: CP152.1, D4.1 (K), D22.1 (K), D40.1 (K), D58.1 (K), D76.1 (K), D94.1 (K), D112.1 (K), D130.1 (K), D148.1 (K), D166.1 (K), D184.1 (K)
/Screen/CS5: CP146.1, D5.1 (K), D23.1 (K), D41.1 (K), D59.1 (K), D77.1 (K), D95.1 (K), D113.1 (K), D131.1 (K), D149.1 (K), D167.1 (K), D185.1 (K)
/Screen/CS6: CP140.1, D6.1 (K), D24.1 (K), D42.1 (K), D60.1 (K), D78.1 (K), D96.1 (K), D114.1 (K), D132.1 (K), D150.1 (K), D168.1 (K), D186.1 (K)
/Screen/CS7: CP134.1, D7.1 (K), D25.1 (K), D43.1 (K), D61.1 (K), D79.1 (K), D97.1 (K), D115.1 (K), D133.1 (K), D151.1 (K), D169.1 (K), D187.1 (K)
/Screen/CS8: CP128.1, D8.1 (K), D26.1 (K), D44.1 (K), D62.1 (K), D80.1 (K), D98.1 (K), D116.1 (K), D134.1 (K), D152.1 (K), D170.1 (K), D188.1 (K)
/Screen/CS9: CP122.1, D9.1 (K), D27.1 (K), D45.1 (K), D63.1 (K), D81.1 (K), D99.1 (K), D117.1 (K), D135.1 (K), D153.1 (K), D171.1 (K), D189.1 (K)
/Screen/CS10: CP116.1, D10.1 (K), D28.1 (K), D46.1 (K), D64.1 (K), D82.1 (K), D100.1 (K), D118.1 (K), D136.1 (K), D154.1 (K), D172.1 (K), D190.1 (K)
/Screen/CS11: CP110.1, D11.1 (K), D29.1 (K), D47.1 (K), D65.1 (K), D83.1 (K), D101.1 (K), D119.1 (K), D137.1 (K), D155.1 (K), D173.1 (K), D191.1 (K)
/Screen/CS12: CP104.1, D12.1 (K), D30.1 (K), D48.1 (K), D66.1 (K), D84.1 (K), D102.1 (K), D120.1 (K), D138.1 (K), D156.1 (K), D174.1 (K), D192.1 (K)
/Screen/CS13: CP98.1, D13.1 (K), D31.1 (K), D49.1 (K), D67.1 (K), D85.1 (K), D103.1 (K), D121.1 (K), D139.1 (K), D157.1 (K), D175.1 (K), D193.1 (K)
/Screen/CS14: CP92.1, D14.1 (K), D32.1 (K), D50.1 (K), D68.1 (K), D86.1 (K), D104.1 (K), D122.1 (K), D140.1 (K), D158.1 (K), D176.1 (K), D194.1 (K)
/Screen/CS15: CP86.1, D15.1 (K), D33.1 (K), D51.1 (K), D69.1 (K), D87.1 (K), D105.1 (K), D123.1 (K), D141.1 (K), D159.1 (K), D177.1 (K), D195.1 (K)
/Screen/CS16: CP80.1, D16.1 (K), D34.1 (K), D52.1 (K), D70.1 (K), D88.1 (K), D106.1 (K), D124.1 (K), D142.1 (K), D160.1 (K), D178.1 (K), D196.1 (K)
/Screen/CS17: CP74.1, D17.1 (K), D35.1 (K), D53.1 (K), D71.1 (K), D89.1 (K), D107.1 (K), D125.1 (K), D143.1 (K), D161.1 (K), D179.1 (K), D197.1 (K)
/Screen/CS18: CP68.1, D18.1 (K), D36.1 (K), D54.1 (K), D72.1 (K), D90.1 (K), D108.1 (K), D126.1 (K), D144.1 (K), D162.1 (K), D180.1 (K), D198.1 (K)
/Screen/SW1: CP62.1, D1.2 (A), D2.2 (A), D3.2 (A), D4.2 (A), D5.2 (A), D6.2 (A), D7.2 (A), D8.2 (A), D9.2 (A), D10.2 (A), D11.2 (A), D12.2 (A), D13.2 (A), D14.2 (A), D15.2 (A), D16.2 (A), D17.2 (A), D18.2 (A)
/Screen/SW2: CP56.1, D19.2 (A), D20.2 (A), D21.2 (A), D22.2 (A), D23.2 (A), D24.2 (A), D25.2 (A), D26.2 (A), D27.2 (A), D28.2 (A), D29.2 (A), D30.2 (A), D31.2 (A), D32.2 (A), D33.2 (A), D34.2 (A), D35.2 (A), D36.2 (A)
/Screen/SW3: CP50.1, D37.2 (A), D38.2 (A), D39.2 (A), D40.2 (A), D41.2 (A), D42.2 (A), D43.2 (A), D44.2 (A), D45.2 (A), D46.2 (A), D47.2 (A), D48.2 (A), D49.2 (A), D50.2 (A), D51.2 (A), D52.2 (A), D53.2 (A), D54.2 (A)
/Screen/SW4: CP44.1, D55.2 (A), D56.2 (A), D57.2 (A), D58.2 (A), D59.2 (A), D60.2 (A), D61.2 (A), D62.2 (A), D63.2 (A), D64.2 (A), D65.2 (A), D66.2 (A), D67.2 (A), D68.2 (A), D69.2 (A), D70.2 (A), D71.2 (A), D72.2 (A)
/Screen/SW5: CP38.1, D73.2 (A), D74.2 (A), D75.2 (A), D76.2 (A), D77.2 (A), D78.2 (A), D79.2 (A), D80.2 (A), D81.2 (A), D82.2 (A), D83.2 (A), D84.2 (A), D85.2 (A), D86.2 (A), D87.2 (A), D88.2 (A), D89.2 (A), D90.2 (A)
/Screen/SW6: CP32.1, D91.2 (A), D92.2 (A), D93.2 (A), D94.2 (A), D95.2 (A), D96.2 (A), D97.2 (A), D98.2 (A), D99.2 (A), D100.2 (A), D101.2 (A), D102.2 (A), D103.2 (A), D104.2 (A), D105.2 (A), D106.2 (A), D107.2 (A), D108.2 (A)
/Screen/SW7: CP26.1, D109.2 (A), D110.2 (A), D111.2 (A), D112.2 (A), D113.2 (A), D114.2 (A), D115.2 (A), D116.2 (A), D117.2 (A), D118.2 (A), D119.2 (A), D120.2 (A), D121.2 (A), D122.2 (A), D123.2 (A), D124.2 (A), D125.2 (A), D126.2 (A)
/Screen/SW8: CP20.1, D127.2 (A), D128.2 (A), D129.2 (A), D130.2 (A), D131.2 (A), D132.2 (A), D133.2 (A), D134.2 (A), D135.2 (A), D136.2 (A), D137.2 (A), D138.2 (A), D139.2 (A), D140.2 (A), D141.2 (A), D142.2 (A), D143.2 (A), D144.2 (A)
/Screen/SW9: CP14.1, D145.2 (A), D146.2 (A), D147.2 (A), D148.2 (A), D149.2 (A), D150.2 (A), D151.2 (A), D152.2 (A), D153.2 (A), D154.2 (A), D155.2 (A), D156.2 (A), D157.2 (A), D158.2 (A), D159.2 (A), D160.2 (A), D161.2 (A), D162.2 (A)
/Screen/SW10: CP8.1, D163.2 (A), D164.2 (A), D165.2 (A), D166.2 (A), D167.2 (A), D168.2 (A), D169.2 (A), D170.2 (A), D171.2 (A), D172.2 (A), D173.2 (A), D174.2 (A), D175.2 (A), D176.2 (A), D177.2 (A), D178.2 (A), D179.2 (A), D180.2 (A)
/Screen/SW11: CP2.1, D181.2 (A), D182.2 (A), D183.2 (A), D184.2 (A), D185.2 (A), D186.2 (A), D187.2 (A), D188.2 (A), D189.2 (A), D190.2 (A), D191.2 (A), D192.2 (A), D193.2 (A), D194.2 (A), D195.2 (A), D196.2 (A), D197.2 (A), D198.2 (A)
GND: C1.2, C2.2, C3.2, C4.2, C5.2, C6.2, C7.2, C8.2, C9.2, C10.2, C11.2, C12.2, C13.2, C14.2, C15.2, C16.2, C17.2, C18.2, C19.2, C20.2, C21.2, C22.2, C23.2, C24.2, C25.2, C26.2, C27.2, C28.2, C29.2, C30.2, C31.2, C32.2, C33.2, C34.2, C35.2, C36.2, C37.2, C38.2, C39.2, C40.2, C41.2, C42.2, C43.2, C44.2, J1.4, J1.MP (MountPin), R6.2, R8.1, R9.1, R10.1, R16.2, R18.1, R20.1, R26.2, R28.1, R36.2, R38.1, R39.1, U1.16 (PGND), U1.23 (GND), U1.41 (PAD), U2.16 (PGND), U2.23 (GND), U2.41 (PAD), U3.16 (PGND), U3.23 (GND), U3.41 (PAD), U4.16 (PGND), U4.23 (GND), U4.41 (PAD)
unnamed: C19.1, R5.2, R6.1, U1.26 (SDB)
unnamed: C26.1, R15.2, R16.1, U2.26 (SDB)
unnamed: C33.1, R25.2, R26.1, U3.26 (SDB)
unnamed: C44.1, R35.2, R36.1, U4.26 (SDB)
unnamed: R1.2, R4.2, U1.27 (SCL)
unnamed: R2.2, R3.2, U1.28 (SDA)
unnamed: R7.2, U1.30 (SYNC)
unnamed: R8.2, U1.29 (ISET)
unnamed: R9.2, U1.24 (ADDR2)
unnamed: R10.2, U1.25 (ADDR1)
unnamed: R11.2, R14.2, U2.27 (SCL)
unnamed: R12.2, R13.2, U2.28 (SDA)
unnamed: R17.2, U2.30 (SYNC)
unnamed: R18.2, U2.29 (ISET)
unnamed: R19.2, U2.24 (ADDR2)
unnamed: R20.2, U2.25 (ADDR1)
unnamed: R21.2, R24.2, U3.27 (SCL)
unnamed: R22.2, R23.2, U3.28 (SDA)
unnamed: R27.2, U3.30 (SYNC)
unnamed: R28.2, U3.29 (ISET)
unnamed: R29.2, U3.24 (ADDR2)
unnamed: R30.2, U3.25 (ADDR1)
unnamed: R31.2, R34.2, U4.27 (SCL)
unnamed: R32.2, R33.2, U4.28 (SDA)
unnamed: R37.2, U4.30 (SYNC)
unnamed: R38.2, U4.29 (ISET)
unnamed: R39.2, U4.24 (ADDR2)
unnamed: R40.2, U4.25 (ADDR1)

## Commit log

2022-05-12 added the LED driver IC
2022-05-13 added the datasheet of the LED driver
2022-05-19 all the routing is done
2022-07-21 last commit before migrating to IS31FL3731
2022-07-21 added IS31FL3731 and, edited its page
2022-12-12 last commit before 0805 migration
2022-12-13 split the board to two boards: nixie-panel and nixie-CU
2022-12-19 routing is done (mostly). Paused routing, waiting for spaceClaim
2022-12-24 the routing and fine touching is done. Ready for production
2022-12-29 submodule issue...
2022-12-29 readded the submodules
2022-12-29 conflict between submodules, needs merging
2022-12-30 created two individual enzyme submodules for each circuit project
2023-01-01 created a documentation structure
2023-01-02 created file system for taking notes
2023-01-02 Update README.md
    small change on Readme.md
2023-01-02 trying to add image to an md file
2023-01-02 trying to use html scripts on .md files
2023-01-02 added html codes to the readme file
2023-01-02 started to take note about the LED Driver
2023-01-02 added LED driver circuit pictures
2023-01-03 Added some general overview about ESP32-S3
2023-01-03 added ESP32-S3 Adafruit board to the Notes
2023-01-03 ESP32-S3-Mini front view
2023-01-04 Updated the ESP-32 note
2023-01-04 added a picture of the Feather board's pinout
2023-01-04 typo on ESP32-S3 document
2023-01-05 added recursive clone command to the readme file
2023-01-06 found the necessary libs for s3 esp32 on GitHub
2023-01-07 added macOS guide for esp32 repos
2023-01-07 update on esp32 library installation guide
2023-01-07 python command correction
2023-01-07 python terminal logs, picture in Notes
2023-01-07 update on esp32 note, board selector
2023-01-08 board selector picture
2023-01-08 added note about Adafruit drivers
2023-01-09 added some html notes
2023-01-10 Added the first software
2023-01-12 added the first html file
2023-01-14 update on html example
2023-01-16 ESP32-S3 first code trails
2023-01-16 first commit from work computer / test commit
2023-01-16 First light from the panel! All works like a charm!
2023-01-16 both 0x74 and 0x77 are working spontaneously
2023-01-17 changed the way of reaching to the pixels
2023-01-18 connected all the drivers to a single I2C bus
2023-01-19 trying to add an alternative SCLK line
2023-01-20 working version of 2 individual clk on single I2C
2023-01-20 copied the modified libraries and created the HAL layer
2023-01-20 HAL Layer is active and shows the demo
2023-01-21 trying to add GFX objects to the source code
2023-01-22 added the GFX libs succesfully, trying to add a pixel convertion
2023-01-22 stable commit, with circle draw animation
2023-01-23 added an equation to make gamma correction and it works
2023-01-25 update on syntax of Gamma correction
2023-01-27 tested the speed of the CPU. Looks as fast as described
2023-01-27 improved I2C speed. At least 32 times faster now
2023-01-27 tried interpolation with 5 pixels, looks better but flickering
2023-01-28 interpolation works like a charm!
2023-01-31 implementing GFX font files...
2023-02-01 first font trial, changed com buffer length
2023-02-01 cleaned the HAL layer from magic numbers
2023-02-01 cleaned the code of the LED Driver
